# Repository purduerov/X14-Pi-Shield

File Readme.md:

# Readme for X14-Pi-Shield

Whenever you make a new part, download the datasheet and save it here _**and**_ with the part in the parts library

Always pull other people's changes before beginning to work
`git pull`

Be sure to push your changes after  working on them. Run:
1. `git add .` to add any files in this directory or a subdirectory
or `git add -u` to add any modified files
2. (Optional) `git clean -nX` to see what ignored files can be removed
	`git clean -fX` removes ignored files (Eagle backups)
3. `git commit -m "helpful commit message"` with a description of the work that you did
4. `git push` to push your work to github

Other helpful commands
* `git status` says information about modified and staged files
* `git log` shows the recent commits of the repository
* `git log filename.extension` show the recent commits for just that file
* `git checkout first-couple-letter-of-commit-id` lets you go back to a previous version
* `git checkout master` brings you back to the latest commit
* `git tag` lists the tags
* `git tag -a orderX -m "the version of the board placed for the X'th order"` tag a specific commit
* `git push --tags` needed to push tags to remote
* `git show orderX` show the commit log for the given tag
* `git checkout orderX` go back and interact with the files at the tagged commit

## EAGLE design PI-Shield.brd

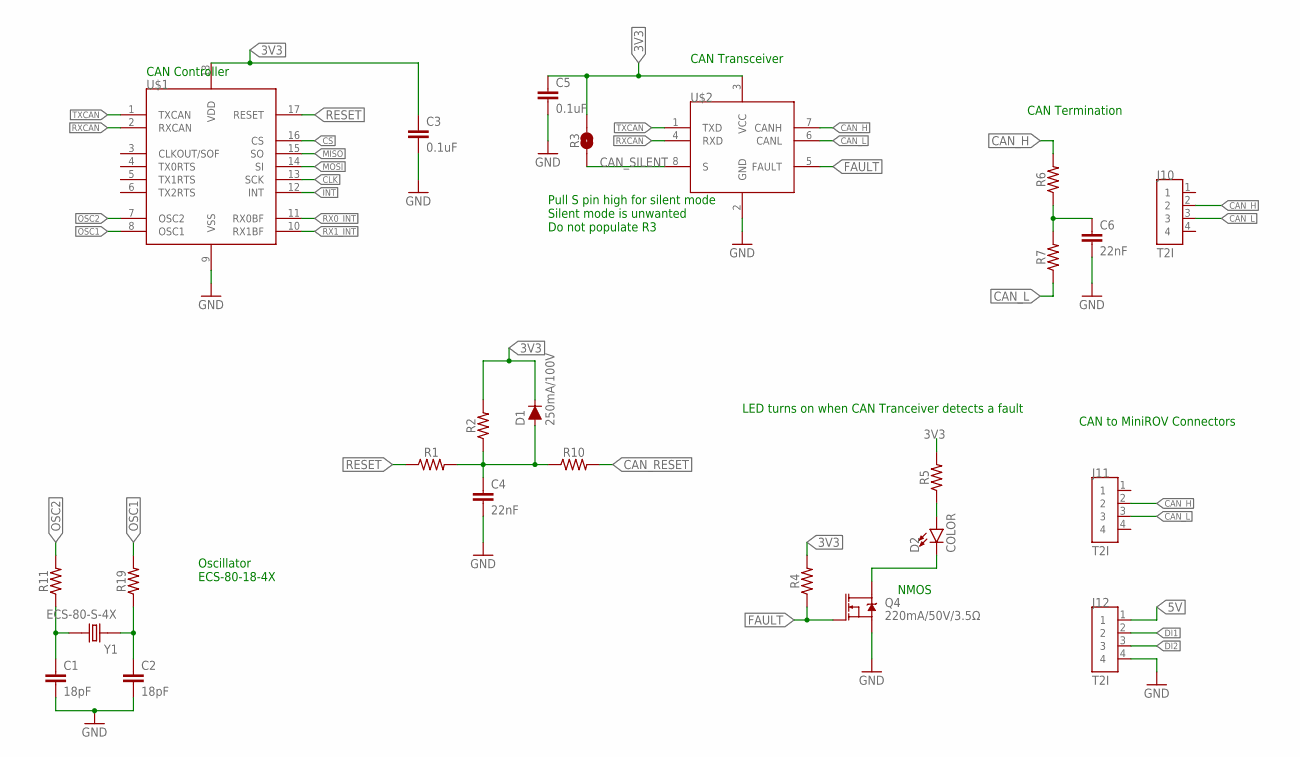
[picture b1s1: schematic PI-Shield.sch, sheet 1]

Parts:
C1, C2: 18pF; 0603
C3, C5: 0.1uF; 0603
C4, C6: 22nF; 0603
D1: 250mA/100V; SOD-323
D2: COLOR; 0805
J10, J11, J12: T2I
Q4: 220mA/50V/3.5Ω; SOT23-3
R1, R2, R4, R5, R6, R7, R10, R11, R19: 0603
R3: JUMPER-SMT_2_NO_SILK; SMT-JUMPER_2_NO_SILK
U$1: MCP2515; SOIC-18
U$2: TCAN337D; SOIC-8
Y1: ECS-80-S-4X; XTAL_ECS-80-S-4X

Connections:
3V3: C3.1, C5.1, D1.C, R2.2, R3.2, R4.2, R5.2, U$1.18 (VDD), U$2.3 (VCC); also elsewhere on the board
5V: J12.1; also elsewhere on the board
CAN_H: J10.2, J11.2, R6.2, U$2.7 (CANH); also elsewhere on the board
CAN_L: J10.3, J11.3, R7.1, U$2.6 (CANL); also elsewhere on the board
CAN_RESET: R10.2; also elsewhere on the board
CAN_SILENT: R3.1, U$2.8 (S)
CAN_TERM_COM: C6.1, R6.1, R7.2
CLK: U$1.13 (SCK); also elsewhere on the board
CS: U$1.16 (CS); also elsewhere on the board
DI1: J12.2; also elsewhere on the board
DI2: J12.3; also elsewhere on the board
FAULT: Q4.1 (G), R4.1, U$2.5 (FAULT)
GND: C1.2, C2.2, C3.2, C4.2, C5.2, C6.2, J12.4, Q4.2 (S), U$1.9 (VSS), U$2.2 (GND); also elsewhere on the board
INT: U$1.12 (INT); also elsewhere on the board
MISO: U$1.15 (SO); also elsewhere on the board
MOSI: U$1.14 (SI); also elsewhere on the board
unnamed: C1.1, R11.1, Y1.2
unnamed: C2.1, R19.1, Y1.1
unnamed: D2.C, Q4.3 (D)
unnamed: D2.A, R5.1
OSC1: R19.2, U$1.8 (OSC1)
OSC2: R11.2, U$1.7 (OSC2)
RESET: R1.1, U$1.17 (RESET)
RESET_MID: C4.1, D1.A, R1.2, R2.1, R10.1
RX0_INT: U$1.11 (RX0BF); also elsewhere on the board
RX1_INT: U$1.10 (RX1BF); also elsewhere on the board
RXCAN: U$1.2 (RXCAN), U$2.4 (RXD)
TXCAN: U$1.1 (TXCAN), U$2.1 (TXD)

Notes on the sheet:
Oscillator ECS-80-18-4X
CAN Termination
CAN to MiniROV Connectors
NMOS
CAN Controller
CAN Transceiver
Pull S pin high for silent mode Silent mode is unwanted Do not populate R3
LED turns on when CAN Tranceiver detects a fault

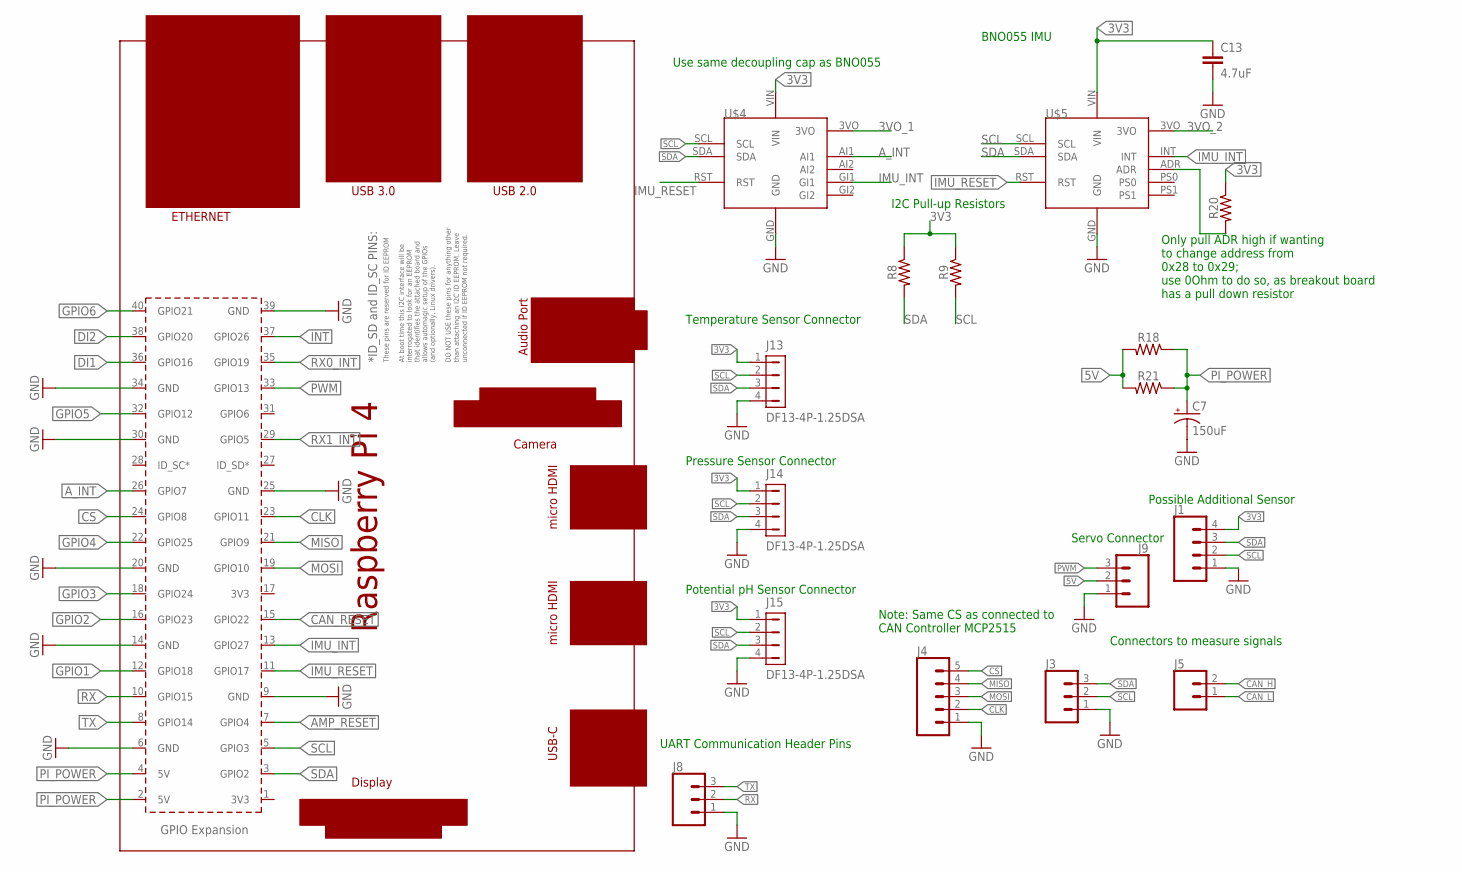
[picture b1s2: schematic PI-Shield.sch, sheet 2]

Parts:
C7: 150uF; 2917(7343-31-METRIC)
C13: 4.7uF; 0603
J1: CONN_04; 1X04
J3, J8, J9: CONN_03; 1X03
J4: CONN_05; 1X05
J5: CONN_02; 1X02
J13, J14, J15: DF13-4P-1.25DSA
R8, R9, R18, R20, R21: 0603
U$4: ADAFRUIT-FXOS8700-FXAS21002
U$5: ADAFRUIT-BNO055
U$8: RPI4

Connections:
3V3: C13.1, J1.4, J13.1, J14.1, J15.1, R8.1, R9.1, R20.1, U$4.VIN, U$5.VIN; also elsewhere on the board
3VO_1: U$4.3VO
3VO_2: U$5.3VO
5V: J9.2, R18.2, R21.2; also elsewhere on the board
!AMP_RESET: U$8.7 (GPIO4); also elsewhere on the board
A_INT: U$4.AI1, U$8.26 (GPIO7)
CAN_H: J5.2; also elsewhere on the board
CAN_L: J5.1; also elsewhere on the board
CAN_RESET: U$8.15 (GPIO22); also elsewhere on the board
CLK: J4.2, U$8.23 (GPIO11); also elsewhere on the board
CS: J4.5, U$8.24 (GPIO8); also elsewhere on the board
DI1: U$8.36 (GPIO16); also elsewhere on the board
DI2: U$8.38 (GPIO20); also elsewhere on the board
GND: C7.-, C13.2, J1.1, J3.1, J4.1, J8.1, J9.1, J13.4, J14.4, J15.4, U$4.GND, U$5.GND, U$8.6 (GND), U$8.9 (GND), U$8.14 (GND), U$8.20 (GND), U$8.25 (GND), U$8.30 (GND), U$8.34 (GND), U$8.39 (GND); also elsewhere on the board
GPIO1: U$8.12 (GPIO18); also elsewhere on the board
GPIO2: U$8.16 (GPIO23); also elsewhere on the board
GPIO3: U$8.18 (GPIO24); also elsewhere on the board
GPIO4: U$8.22 (GPIO25); also elsewhere on the board
GPIO5: U$8.32 (GPIO12); also elsewhere on the board
GPIO6: U$8.40 (GPIO21); also elsewhere on the board
IMU_INT: U$4.GI1, U$5.INT, U$8.13 (GPIO27)
IMU_RESET: U$4.RST, U$5.RST, U$8.11 (GPIO17)
INT: U$8.37 (GPIO26); also elsewhere on the board
MISO: J4.4, U$8.21 (GPIO9); also elsewhere on the board
MOSI: J4.3, U$8.19 (GPIO10); also elsewhere on the board
unnamed: R20.2, U$5.ADR
PI_POWER: C7.+, R18.1, R21.1, U$8.2 (5V), U$8.4 (5V)
PWM: J9.3, U$8.33 (GPIO13)
RX: J8.2, U$8.10 (GPIO15)
RX0_INT: U$8.35 (GPIO19); also elsewhere on the board
RX1_INT: U$8.29 (GPIO5); also elsewhere on the board
SCL: J1.2, J3.2, J13.2, J14.2, J15.2, R9.2, U$4.SCL, U$5.SCL, U$8.5 (GPIO3); also elsewhere on the board
SDA: J1.3, J3.3, J13.3, J14.3, J15.3, R8.2, U$4.SDA, U$5.SDA, U$8.3 (GPIO2); also elsewhere on the board
TX: J8.3, U$8.8 (GPIO14)

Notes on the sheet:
Connectors to measure signals
Temperature Sensor Connector
Pressure Sensor Connector
Potential pH Sensor Connector
BNO055 IMU
Possible Additional Sensor
UART Communication Header Pins
Servo Connector
Only pull ADR high if wanting to change address from 0x28 to 0x29; use 0Ohm to do so, as breakout board has a pull down resistor
Use same decoupling cap as BNO055
I2C Pull-up Resistors
Note: Same CS as connected to CAN Controller MCP2515

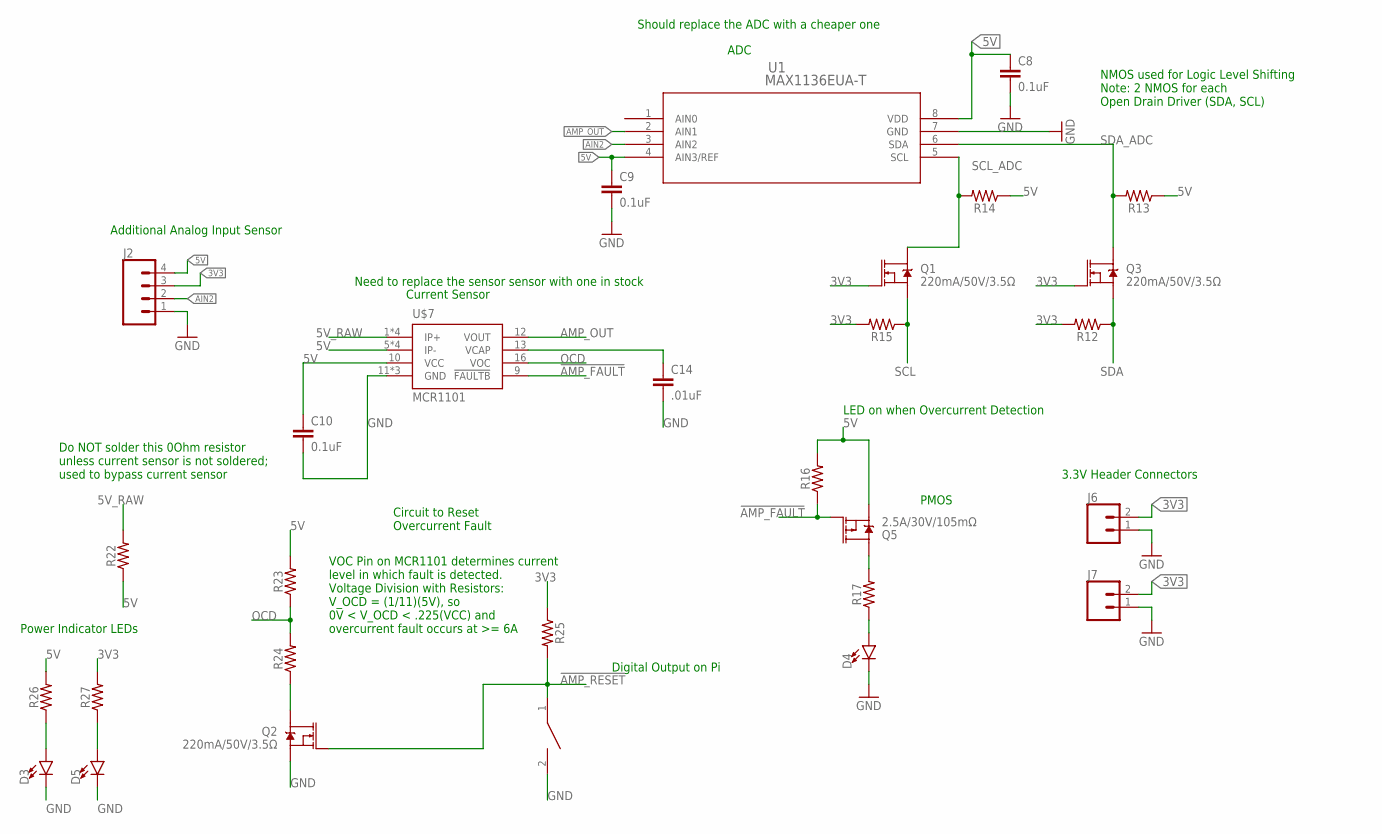
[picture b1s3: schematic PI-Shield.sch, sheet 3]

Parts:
C8, C9, C10: 0.1uF; 0603
C14: .01uF; 0603
D3, D4, D5: LED0603; LED-0603
J2: CONN_04; 1X04
J6, J7: CONN_02; 1X02
Q1, Q2, Q3: 220mA/50V/3.5Ω; SOT23-3
Q5: 2.5A/30V/105mΩ; SOT23-3
R12, R13, R14, R15, R16, R17, R22, R23, R24, R25, R26, R27: 0603
U1: MAX1136EUA-T; 21-0036K
U$6: DISCRETECOMPONENTS_SWITCH; DISCRETECOMPONENTS_SW_2512
U$7: MCR1101; SOIC-16

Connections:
3V3: J2.3, J6.2, J7.2, Q1.1 (G), Q3.1 (G), R12.2, R15.2, R25.1, R27.2; also elsewhere on the board
5V: C8.1, C9.1, C10.1, J2.4, Q5.2 (S), R13.1, R14.1, R16.2, R22.1, R23.2, R26.2, U1.4 (AIN3/REF), U1.8 (VDD), U$7.5 (IP-), U$7.6 (IP-), U$7.7 (IP-), U$7.8 (IP-), U$7.10 (VCC); also elsewhere on the board
5V_RAW: R22.2, U$7.1 (IP+), U$7.2 (IP+), U$7.3 (IP+), U$7.4 (IP+)
!AMP_FAULT: Q5.1 (G), R16.1, U$7.9 (!FAULTB)
!AMP_RESET: Q2.1 (G), R25.2, U$6.1; also elsewhere on the board
AIN2: J2.2, U1.3 (AIN2)
AMP_OUT: U1.2 (AIN1), U$7.12 (VOUT)
GND: C8.2, C9.2, C10.2, C14.2, D3.C, D4.C, D5.C, J2.1, J6.1, J7.1, Q2.2 (S), U1.7 (GND), U$6.2, U$7.11 (GND), U$7.14 (GND), U$7.15 (GND); also elsewhere on the board
unnamed: C14.1, U$7.13 (VCAP)
unnamed: D3.A, R26.1
unnamed: Q5.3 (D), R17.2
unnamed: D4.A, R17.1
unnamed: D5.A, R27.1
unnamed: Q2.3 (D), R24.1
OCD: R23.1, R24.2, U$7.16 (VOC)
SCL: Q1.2 (S), R15.1; also elsewhere on the board
SCL_ADC: Q1.3 (D), R14.2, U1.5 (SCL)
SDA: Q3.2 (S), R12.1; also elsewhere on the board
SDA_ADC: Q3.3 (D), R13.2, U1.6 (SDA)

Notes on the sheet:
ADC
Additional Analog Input Sensor
3.3V Header Connectors
PMOS
LED on when Overcurrent Detection
NMOS used for Logic Level Shifting Note: 2 NMOS for each Open Drain Driver (SDA, SCL)
Do NOT solder this 0Ohm resistor unless current sensor is not soldered; used to bypass current sensor
Current Sensor
Circuit to Reset Overcurrent Fault
Need to replace the sensor sensor with one in stock
Should replace the ADC with a cheaper one
Power Indicator LEDs
VOC Pin on MCR1101 determines current level in which fault is detected. Voltage Division with Resistors: V_OCD = (1/11)(5V), so 0V < V_OCD < .225(VCC) and overcurrent fault occurs at >= 6A
Digital Output on Pi

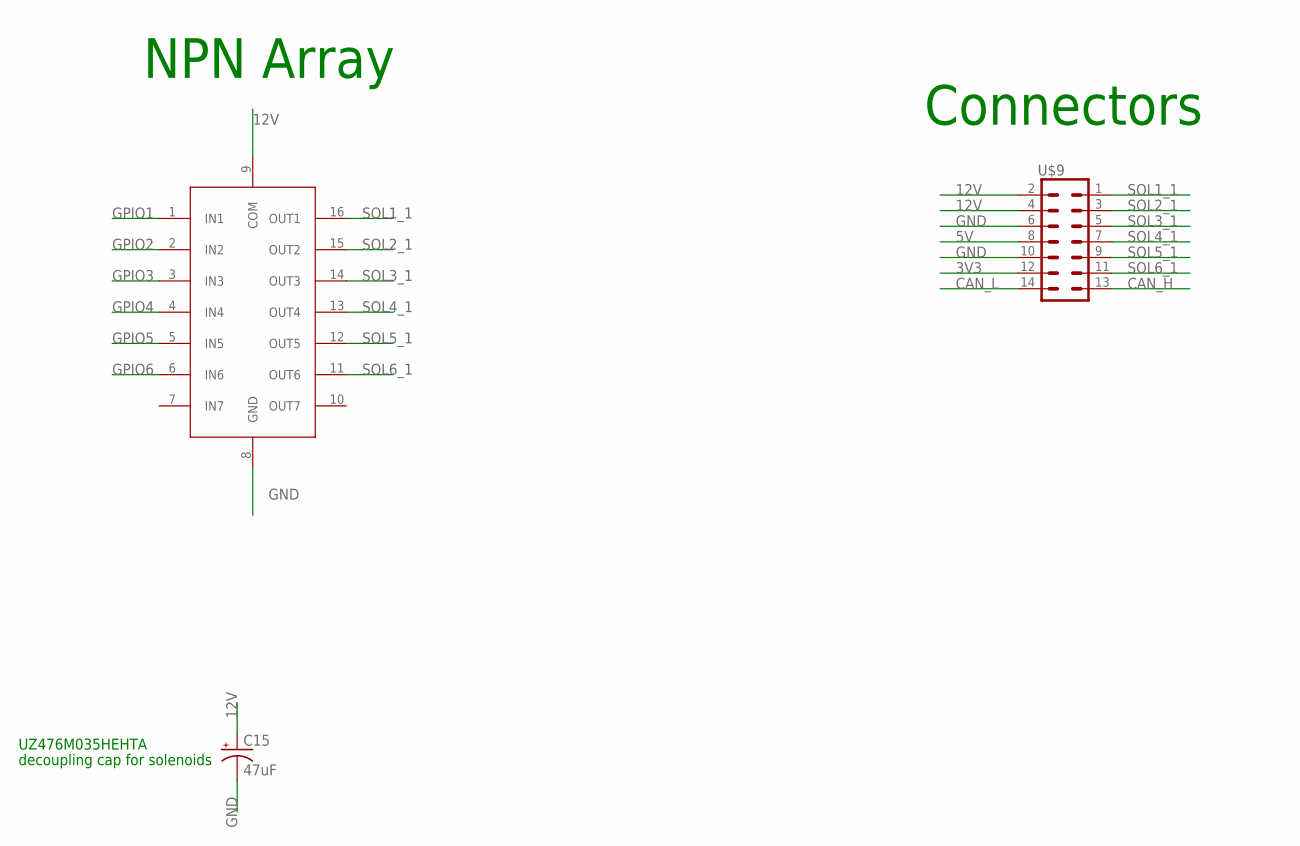
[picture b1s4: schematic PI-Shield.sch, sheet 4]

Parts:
C15: 47uF; PANASONIC_D
U3: ULN2003V12
U$9: 7X_CONN; IPL7X2

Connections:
3V3: U$9.12 (23); also elsewhere on the board
5V: U$9.8 (19); also elsewhere on the board
12V: C15.+, U3.9 (COM), U$9.2 (13), U$9.4 (15)
CAN_H: U$9.13 (1); also elsewhere on the board
CAN_L: U$9.14 (2); also elsewhere on the board
GND: C15.-, U3.8 (GND), U$9.6 (17), U$9.10 (21); also elsewhere on the board
GPIO1: U3.1 (IN1); also elsewhere on the board
GPIO2: U3.2 (IN2); also elsewhere on the board
GPIO3: U3.3 (IN3); also elsewhere on the board
GPIO4: U3.4 (IN4); also elsewhere on the board
GPIO5: U3.5 (IN5); also elsewhere on the board
GPIO6: U3.6 (IN6); also elsewhere on the board
SOL1_1: U3.16 (OUT1), U$9.1 (14)
SOL2_1: U3.15 (OUT2), U$9.3 (16)
SOL3_1: U3.14 (OUT3), U$9.5 (18)
SOL4_1: U3.13 (OUT4), U$9.7 (20)
SOL5_1: U3.12 (OUT5), U$9.9 (22)
SOL6_1: U3.11 (OUT6), U$9.11 (24)

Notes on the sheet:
NPN Array
Connectors
decoupling cap for solenoids
UZ476M035HEHTA

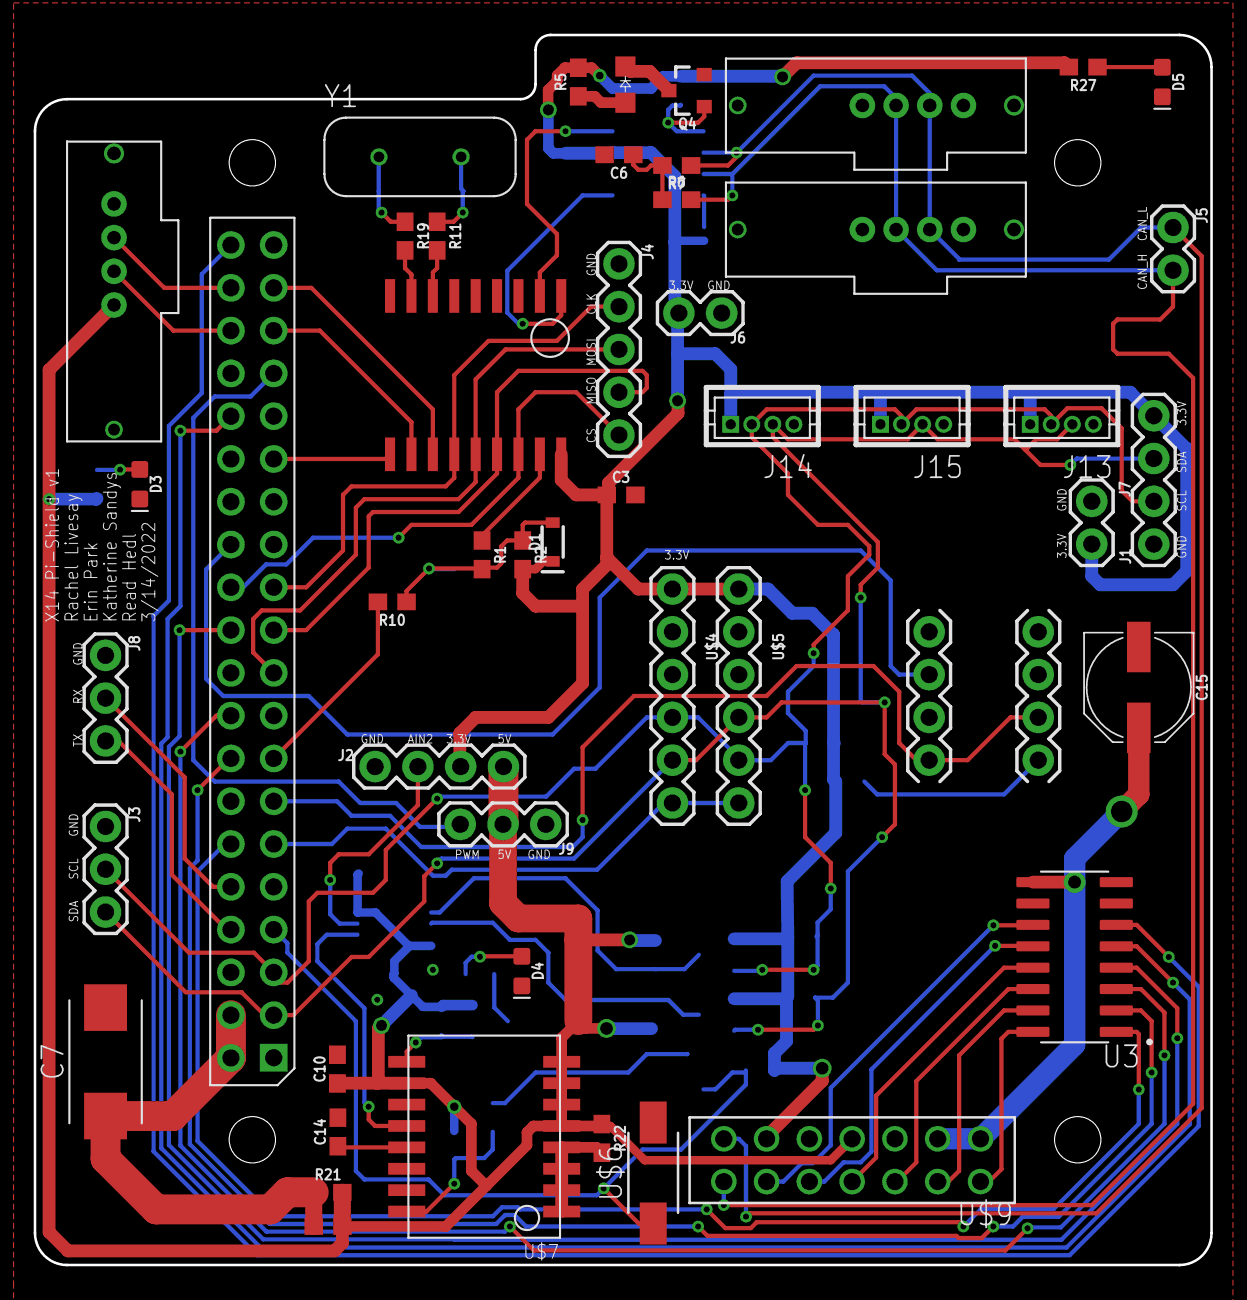
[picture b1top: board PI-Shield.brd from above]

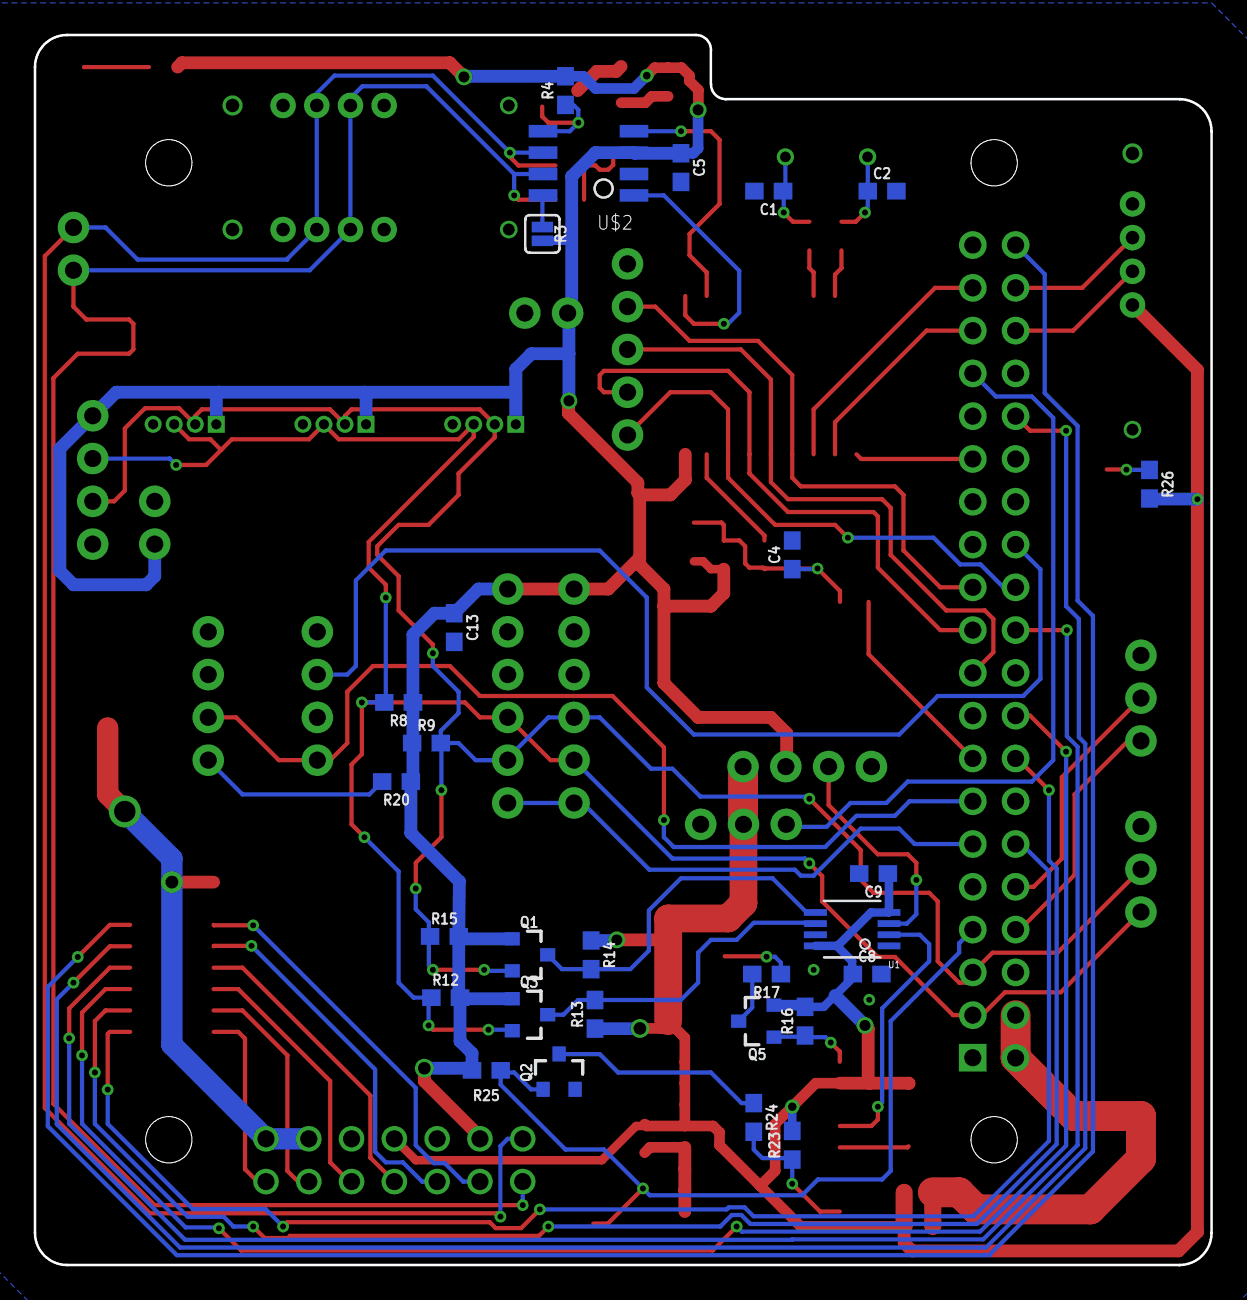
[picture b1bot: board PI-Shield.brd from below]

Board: 2 copper layers, 69.8 x 73.0 mm, 76 parts (28 on the bottom side), 65 nets.

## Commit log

2021-09-18 readme+gitignore
2021-10-06 initial commit
    (finally, needed to reinstall GitHub :P)
    [Changes: merged solenoid and shield schematics, removed STM]
    [To Do: Add connectors for 12V to solenoid, make it look pretty]
2021-10-23 Schematic Update
    Changes: [Added GPIO extender, wired up to SDA/SCL; removed owos]
2021-11-06 Sch Update, Added Board
    [Changes: Removed micro-USB, Added 47uF cap between 12v and GND, added new connector to backplane (added lib to X-14-parts-library), A0-A2 on GPIO Expander grounded.]
    [To Do: Add TVS diode between SCL/SDA, Connect open drain output on GPIO expander.]
2021-11-30 Board Update
    Changes: [Reduced backplane connector from 26->12 positions, added board outline matching last year's, placement of components]
    To Do: [Routing, which should be done within next 24 hrs :P]
2021-11-30 Schematic Update
    Changes: [FREAKING FORGOT TO LABEL A PIN >:((((]
2021-12-02 Routing Hard >:(
    Changes: [Started routing,,,,, it's going well???? i dunno, *power polygons*]
2021-12-04 Routing :)
    Change: [bro why this game of flow so hard??]
2021-12-04 Fixed Like 2 Routes smh
2021-12-19 Alumni Design Updates
    Changes: [Trace Matched SCL/SDA & TX/RX, added alumni feedback]
2021-12-30 Update PI-Shield.brd
    fixed errors
2022-01-07 Added CAN to BKP... Silkscreen as well
2022-01-26 STEPS!
2022-03-11 v2 Changes
    Would like to formally apologize for the routing of the GPIO on the bottom of the board. It was necessary, unfortunately.
    Changes: [Removed expander, added LED and Header Labels, really shitty routing.]
2022-03-14 Adjusted Labels
2022-03-14 Adjusted some labels, fixed minor errors
2022-03-14 Replaced R3 with Jumper, exported STEP

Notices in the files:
parts and their libraries:
SparkFun-Capacitors: Licensing: Creative Commons ShareAlike 4.0 International - https://creativecommons.org/licenses/by-sa/4.0
